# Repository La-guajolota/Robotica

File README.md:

# 🤖 Robotics Design Toolkit 
*Resources for comprehensive robot design: Kinematics, Dynamics, Mechanisms and more*

---

A curated repository with tools, algorithms, simulations and educational resources for the design and analysis of robotic systems.

---

## 📂 Folder Structure

This repository is organized into the following main directories:

- **`computes/`**: Contains scripts and algorithms for kinematic and dynamic calculations.
- **`IA/`**: Artificial Intelligence algorithms and examples.
- **`proyects/`**: Various robotics projects, from CAD designs to software implementations.
- **`raspberry5/`**: Scripts and resources for the Raspberry Pi 5.
- **`vision/`**: Computer vision algorithms and examples.

---

## 🚀 Getting Started

To get started with this repository, you can clone it to your local machine:

```bash
git clone https://github.com/your-username/robotics-design-toolkit.git
```

Once cloned, you can explore the different folders and use the resources available in each of them. For more information on how to use the content of a specific folder, please refer to the `README.md` file in that folder.

---

## 🤝 Contributing

Contributions are welcome! If you have any ideas, suggestions or improvements, please open an issue or submit a pull request.

---

## 📜 License

This repository is licensed under the [MIT License](LICENSE).

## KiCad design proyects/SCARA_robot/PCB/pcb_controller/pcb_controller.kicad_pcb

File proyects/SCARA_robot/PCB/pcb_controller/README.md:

# ⚡️ PCB Controller

This directory contains the KiCad project for the robot's controller PCB.

---

## 📂 Files

- **`pcb_controller.kicad_pro`**: The main KiCad project file.
- **`pcb_controller.kicad_sch`**: The schematic for the PCB.
- **`pcb_controller.kicad_pcb`**: The PCB layout.
- **`bom/`**: Contains the Bill of Materials for the PCB.
- **`production/`**: Contains the Gerber files for manufacturing the PCB.
- **`modules.pretty/`**: Contains custom footprints used in the project.
- **`pcb_controller-backups/`**: Contains backups of the project.

---

## 🚀 Usage

You can open the `pcb_controller.kicad_pro` file in KiCad to view and edit the schematic and PCB layout. The Gerber files in the `production` directory can be used to manufacture the PCB.

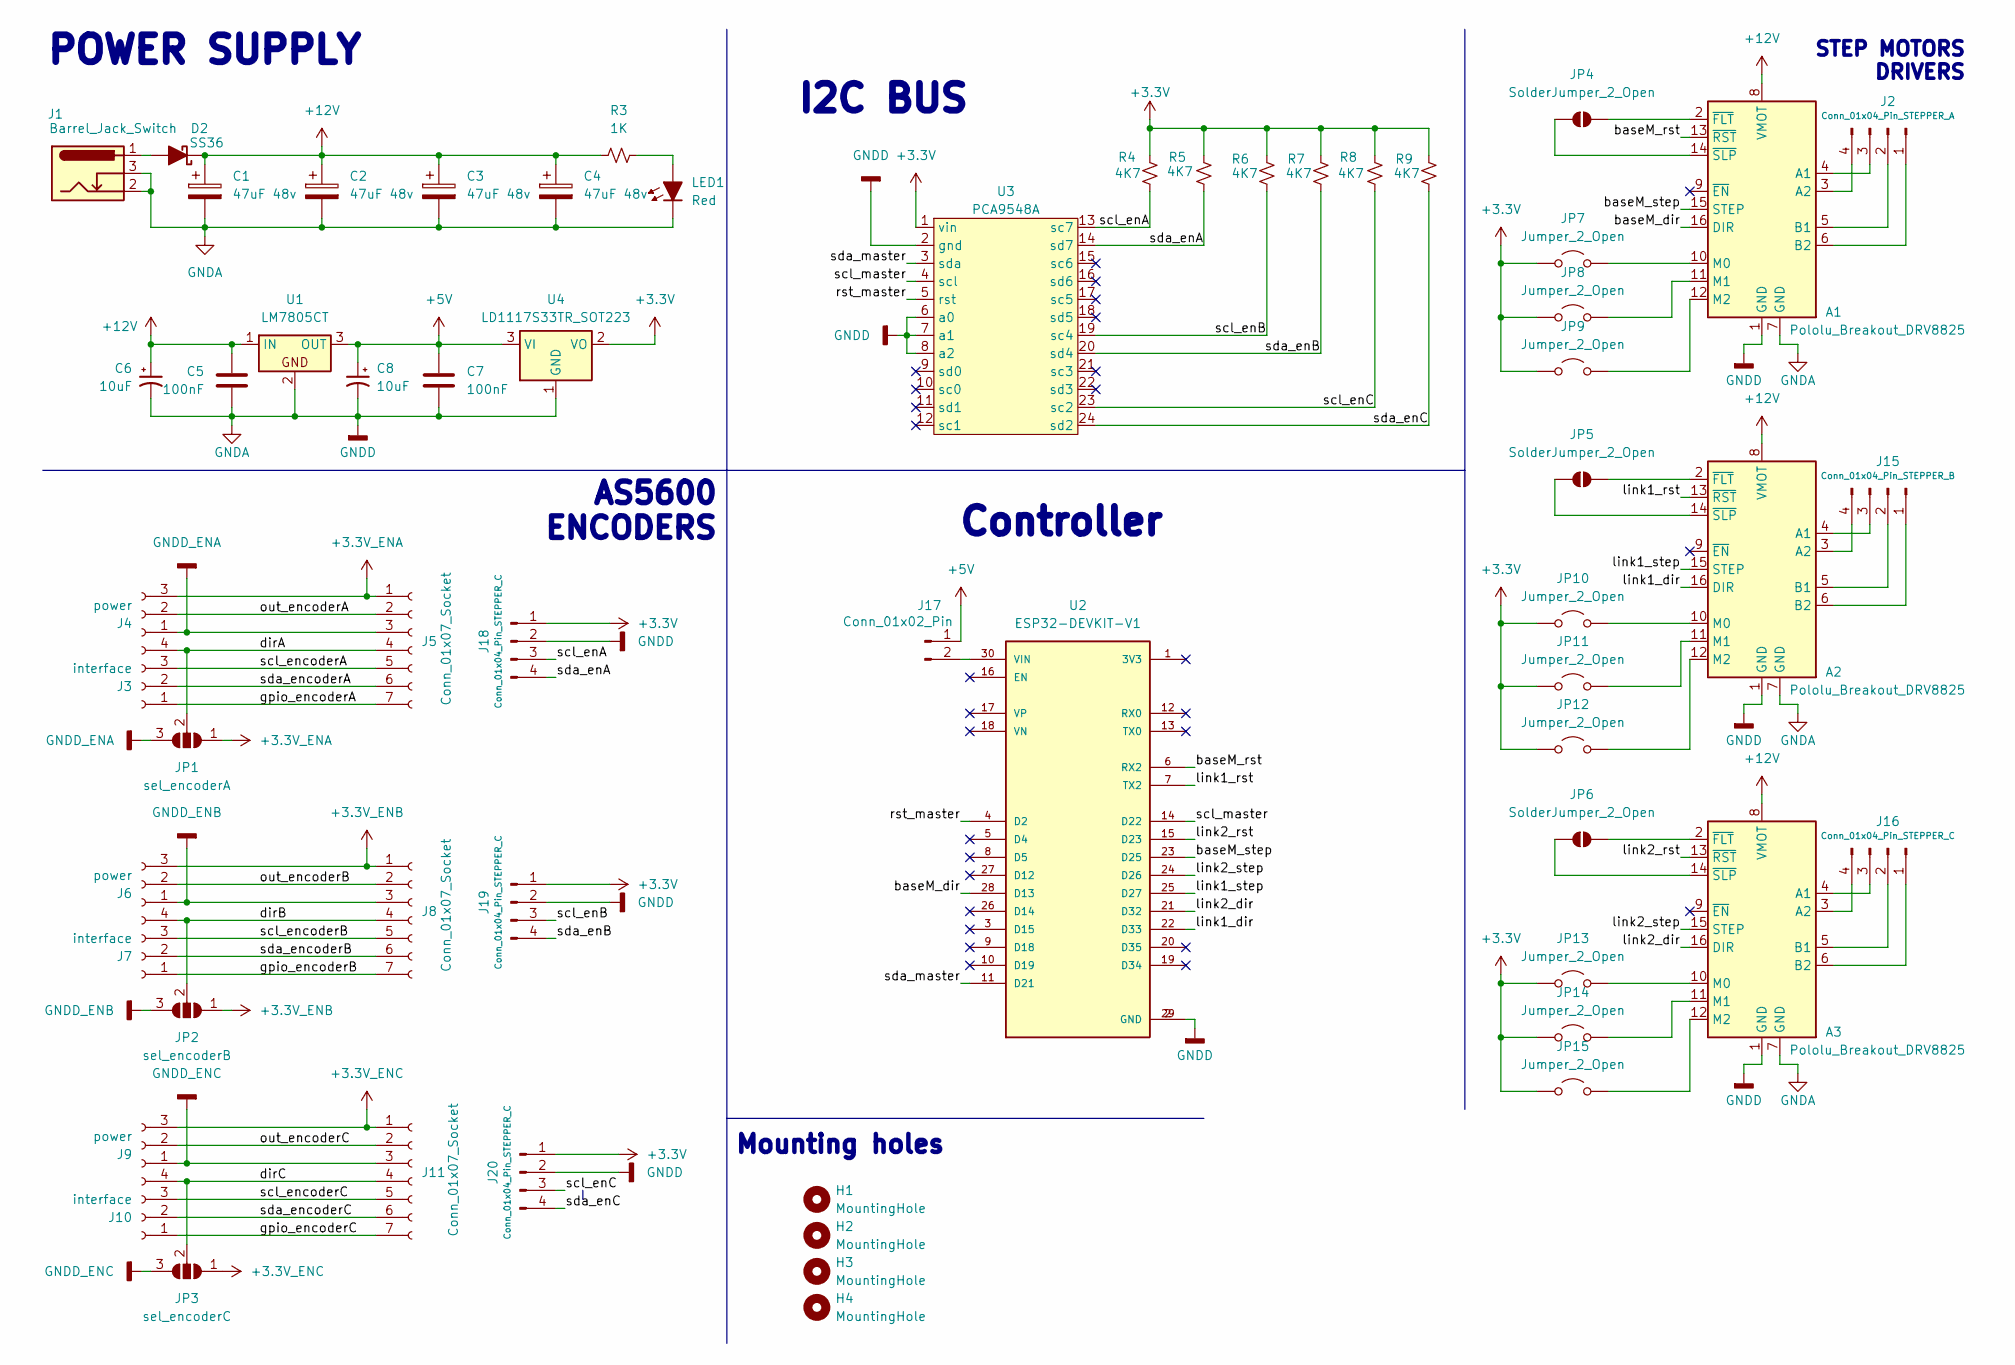
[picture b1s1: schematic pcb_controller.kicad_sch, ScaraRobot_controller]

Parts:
A1, A2, A3: Pololu_Breakout_DRV8825; Pololu_Breakout-16_15.2x20.3mm
C1, C2, C3, C4: 47uF 48v; CP_Radial_D10.0mm_P5.00mm
C5, C7: 100nF; C_Disc_D4.7mm_W2.5mm_P5.00mm
C6, C8: 10uF; CP_Radial_D5.0mm_P2.00mm
D2: SS36; D_2114_3652Metric_Pad1.85x3.75mm_HandSolder
H1, H2, H3, H4: MountingHole; MountingHole_3.2mm_M3_ISO14580
J1: Barrel_Jack_Switch; BarrelJack_CUI_PJ-102AH_Horizontal
J2: Conn_01x04_Pin_STEPPER_A; JST_XH_B4B-XH-AM_1x04_P2.50mm_Vertical
J3, J7, J10: interface; PinHeader_1x04_P2.54mm_Vertical
J4, J6, J9: power; PinHeader_1x03_P2.54mm_Vertical
J5, J8, J11: Conn_01x07_Socket; JST_XH_S7B-XH-A-1_1x07_P2.50mm_Horizontal
J15: Conn_01x04_Pin_STEPPER_B; JST_XH_B4B-XH-AM_1x04_P2.50mm_Vertical
J16, J18, J19, J20: Conn_01x04_Pin_STEPPER_C; JST_XH_B4B-XH-AM_1x04_P2.50mm_Vertical
J17: Conn_01x02_Pin; PinSocket_1x02_P2.54mm_Vertical
JP1: sel_encoderA; SolderJumper-3_P1.3mm_Open_RoundedPad1.0x1.5mm
JP2: sel_encoderB; SolderJumper-3_P1.3mm_Open_RoundedPad1.0x1.5mm
JP3: sel_encoderC; SolderJumper-3_P1.3mm_Open_RoundedPad1.0x1.5mm
JP4, JP5, JP6: SolderJumper_2_Open; SolderJumper-2_P1.3mm_Open_RoundedPad1.0x1.5mm
JP7, JP8, JP9, JP10, JP11, JP12, JP13, JP14, JP15: Jumper_2_Open; Jumper_P2.54mm_D0.7mm
LED1: Red; LED_D5.0mm
R3: 1K; R_Axial_DIN0207_L6.3mm_D2.5mm_P7.62mm_Horizontal
R4, R5, R6, R7, R8, R9: 4K7; R_Axial_DIN0207_L6.3mm_D2.5mm_P10.16mm_Horizontal
U1: LM7805CT; TO-220-3_Horizontal
U2: ESP32-DEVKIT-V1; MODULE_ESP32_DEVKIT_V1; PARTREV N/A
U3: PCA9548A; TCA9548A
U4: LD1117S33TR_SOT223; SOT-223-3_TabPin2

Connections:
+3.3V: J18.1, J19.1, J20.1, JP7.1 (A), JP8.1 (A), JP9.1 (A), JP10.1 (A), JP11.1 (A), JP12.1 (A), JP13.1 (A), JP14.1 (A), JP15.1 (A), R4.1, R5.1, R6.1, R7.1, R8.1, R9.1, U3.1 (vin), U4.2 (VO)
+3.3V_ENA: J4.3, J5.1, JP1.1 (A)
+3.3V_ENB: J6.3, J8.1, JP2.1 (A)
+3.3V_ENC: J9.3, J11.1, JP3.1 (A)
+5V: C7.2, C8.1, J17.1, U1.3 (OUT), U4.3 (VI)
+12V: A1.8 (VMOT), A2.8 (VMOT), A3.8 (VMOT), C1.1, C2.1, C3.1, C4.1, C5.2, C6.1, D2.1 (K), R3.1, U1.1 (IN)
/baseM_dir: A1.16 (DIR), U2.28 (D13)
/baseM_rst: A1.13 (~RST), U2.6 (RX2)
/baseM_step: A1.15 (STEP), U2.23 (D25)
/dirA: J3.4, J5.4, JP1.2 (C)
/dirB: J7.4, J8.4, JP2.2 (C)
/dirC: J10.4, J11.4, JP3.2 (C)
/gpio_encoderA: J3.1, J5.7
/gpio_encoderB: J7.1, J8.7
/gpio_encoderC: J10.1, J11.7
/link1_dir: A2.16 (DIR), U2.22 (D33)
/link1_rst: A2.13 (~RST), U2.7 (TX2)
/link1_step: A2.15 (STEP), U2.25 (D27)
/link2_dir: A3.16 (DIR), U2.21 (D32)
/link2_rst: A3.13 (~RST), U2.15 (D23)
/link2_step: A3.15 (STEP), U2.24 (D26)
/out_encoderA: J4.2, J5.2
/out_encoderB: J6.2, J8.2
/out_encoderC: J9.2, J11.2
/rst_master: U2.4 (D2), U3.5 (rst)
/scl_enA: J18.3, R4.2, U3.13 (sc7)
/scl_enB: J19.3, R6.2, U3.19 (sc4)
/scl_enC: J20.3, R8.2, U3.23 (sc2)
/scl_encoderA: J3.3, J5.5
/scl_encoderB: J7.3, J8.5
/scl_encoderC: J10.3, J11.5
/scl_master: U2.14 (D22), U3.4 (scl)
/sda_enA: J18.4, R5.2, U3.14 (sd7)
/sda_enB: J19.4, R7.2, U3.20 (sd4)
/sda_enC: J20.4, R9.2, U3.24 (sd2)
/sda_encoderA: J3.2, J5.6
/sda_encoderB: J7.2, J8.6
/sda_encoderC: J10.2, J11.6
/sda_master: U2.11 (D21), U3.3 (sda)
GNDA: A1.1 (GND), A1.7 (GND), A2.1 (GND), A2.7 (GND), A3.1 (GND), A3.7 (GND), C1.2, C2.2, C3.2, C4.2, C5.1, C6.2, C7.1, C8.2, J1.2, J1.3, J18.2, J19.2, J20.2, LED1.1 (K), U1.2, U2.2 (GND), U2.29 (GND), U3.2 (gnd), U3.6 (a0), U3.7 (a1), U3.8 (a2), U4.1 (GND)
GNDD_ENA: J4.1, J5.3, JP1.3 (B)
GNDD_ENB: J6.1, J8.3, JP2.3 (B)
GNDD_ENC: J9.1, J11.3, JP3.3 (B)
unnamed: A1.4 (A1), J2.3
unnamed: A1.3 (A2), J2.4
unnamed: A1.5 (B1), J2.2
unnamed: A1.6 (B2), J2.1
unnamed: A1.10 (M0), JP7.2 (B)
unnamed: A1.11 (M1), JP8.2 (B)
unnamed: A1.12 (M2), JP9.2 (B)
unnamed: A1.2 (~FLT), JP4.1 (A)
unnamed: A1.14 (~SLP), JP4.2 (B)
unnamed: A2.4 (A1), J15.3
unnamed: A2.3 (A2), J15.4
unnamed: A2.5 (B1), J15.2
unnamed: A2.6 (B2), J15.1
unnamed: A2.10 (M0), JP10.2 (B)
unnamed: A2.11 (M1), JP11.2 (B)
unnamed: A2.12 (M2), JP12.2 (B)
unnamed: A2.2 (~FLT), JP5.1 (A)
unnamed: A2.14 (~SLP), JP5.2 (B)
unnamed: A3.4 (A1), J16.3
unnamed: A3.3 (A2), J16.4
unnamed: A3.5 (B1), J16.2
unnamed: A3.6 (B2), J16.1
unnamed: A3.10 (M0), JP13.2 (B)
unnamed: A3.11 (M1), JP14.2 (B)
unnamed: A3.12 (M2), JP15.2 (B)
unnamed: A3.2 (~FLT), JP6.1 (A)
unnamed: A3.14 (~SLP), JP6.2 (B)
unnamed: D2.2 (A), J1.1
unnamed: J17.2, U2.30 (VIN)
unnamed: LED1.2 (A), R3.2

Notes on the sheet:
STEP MOTORS DRIVERS
Controller
POWER SUPPLY
I2C BUS
Mounting holes
AS5600 ENCODERS

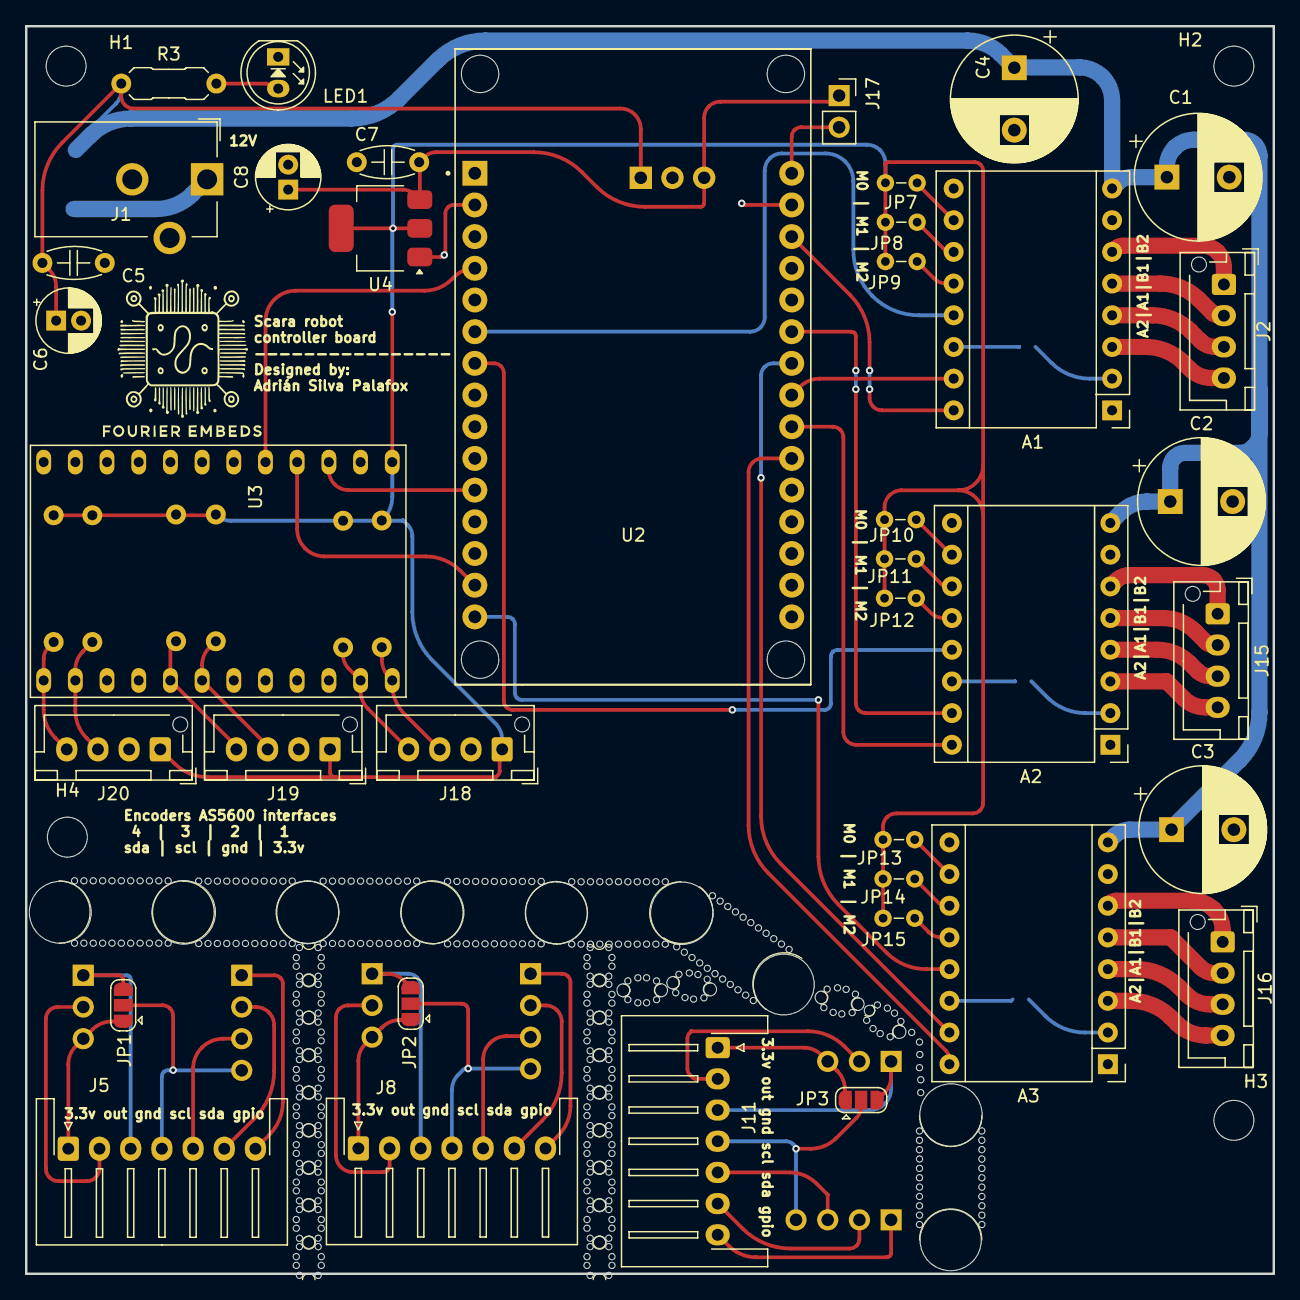
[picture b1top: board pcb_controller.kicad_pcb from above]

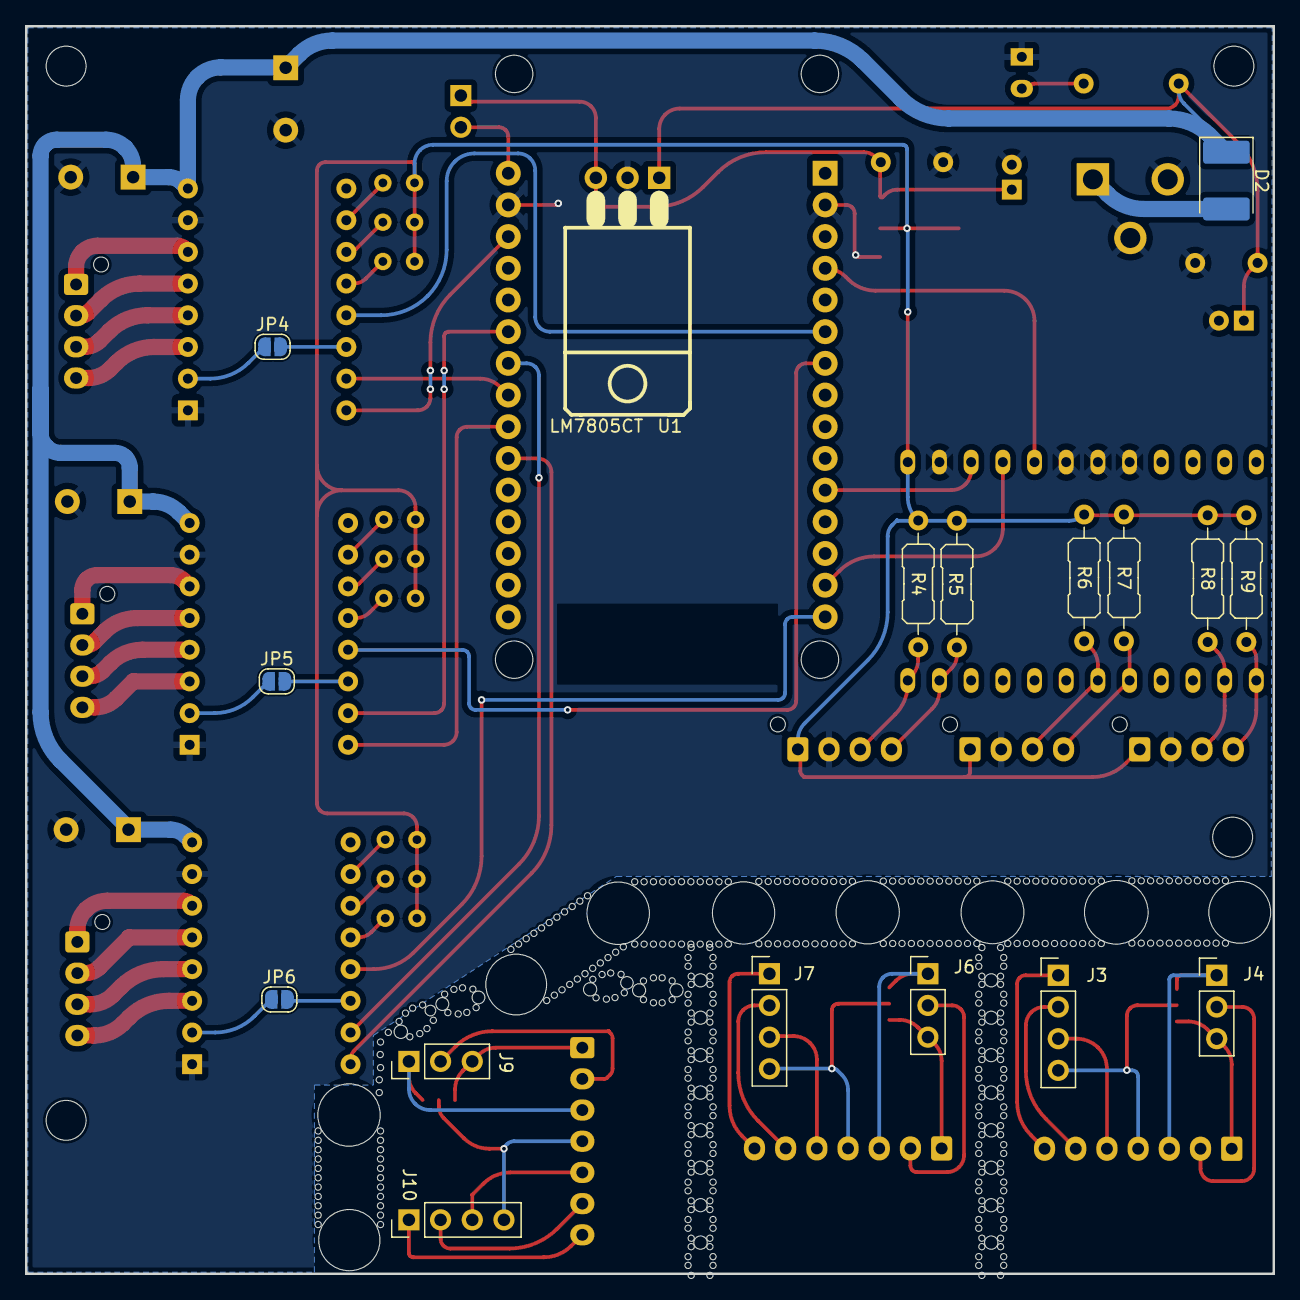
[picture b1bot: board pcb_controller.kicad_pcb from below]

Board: 2 copper layers, 100.0 x 100.0 mm, 90 parts (17 on the bottom side), 73 nets.

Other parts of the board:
Adrián Silva Palafox: LOGO; LOGOFOURIEREMBEDS
mouse-bite-1mm-slot, mouse-bite-1mm-slot#2, mouse-bite-1mm-slot#3, mouse-bite-1mm-slot#4, mouse-bite-1mm-slot#5, mouse-bite-1mm-slot#6, mouse-bite-1mm-slot#7, mouse-bite-1mm-slot#8, mouse-bite-1mm-slot#9, mouse-bite-1mm-slot#10, mouse-bite-1mm-slot#11, mouse-bite-1mm-slot#12, mouse-bite-1mm-slot#13, mouse-bite-1mm-slot#14, mouse-bite-1mm-slot#15, mouse-bite-1mm-slot#16, mouse-bite-1mm-slot#17, mouse-bite-1mm-slot#18, mouse-bite-1mm-slot#19, mouse-bite-1mm-slot#20, mouse-bite-1mm-slot#21, mouse-bite-1mm-slot#22: VAL**; mouse-bite-1mm
mouse-bite-5mm-slot, mouse-bite-5mm-slot#2, mouse-bite-5mm-slot#3, mouse-bite-5mm-slot#4, mouse-bite-5mm-slot#5, mouse-bite-5mm-slot#6, mouse-bite-5mm-slot#7: VAL**; mouse-bite-5mm-slot

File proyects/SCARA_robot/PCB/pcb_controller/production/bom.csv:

Designator,Footprint,Quantity,Value,LCSC Part #
"_6, _5, _4, _3, _2, ",,6,,
"A1, A2, A3",Pololu_Breakout-16_15.2x20.3mm,3,Pololu_Breakout_DRV8825,
"C1, C2, C3, C4",CP_Radial_D10.0mm_P5.00mm,4,47uF 48v,
"C5, C7",C_Disc_D4.7mm_W2.5mm_P5.00mm,2,100nF,
"C6, C8",CP_Radial_D5.0mm_P2.00mm,2,10uF,
D2,2114,1,SS36,
J1,BarrelJack_CUI_PJ-102AH_Horizontal,1,Barrel_Jack_Switch,
"J10, J3, J7",PinHeader_1x04_P2.54mm_Vertical,3,interface,
"J11, J5, J8",JST_XH_S7B-XH-A-1_1x07_P2.50mm_Horizontal,3,Conn_01x07_Socket,
J15,JST_XH_B4B-XH-AM_1x04_P2.50mm_Vertical,1,Conn_01x04_Pin_STEPPER_B,
"J16, J18, J19, J20",JST_XH_B4B-XH-AM_1x04_P2.50mm_Vertical,4,Conn_01x04_Pin_STEPPER_C,
J17,PinSocket_1x02_P2.54mm_Vertical,1,Conn_01x02_Pin,
J2,JST_XH_B4B-XH-AM_1x04_P2.50mm_Vertical,1,Conn_01x04_Pin_STEPPER_A,
"J4, J6, J9",PinHeader_1x03_P2.54mm_Vertical,3,power,
"JP10, JP11, JP12, JP13, JP14, JP15, JP7, JP8, JP9",Jumper_P2.54mm_D0.7mm,9,Jumper_2_Open,
LED1,LED_D5.0mm,1,Red,
"MOUSE-BITE-1MM-SLOT_22, MOUSE-BITE-1MM-SLOT_21, MOUSE-BITE-1MM-SLOT_20, MOUSE-BITE-1MM-SLOT_19, MOUSE-BITE-1MM-SLOT_18, MOUSE-BITE-1MM-SLOT_17, MOUSE-BITE-1MM-SLOT_16, MOUSE-BITE-1MM-SLOT_15, MOUSE-BITE-1MM-SLOT_14, MOUSE-BITE-1MM-SLOT_13, MOUSE-BITE-1MM-SLOT_12, MOUSE-BITE-1MM-SLOT_11, MOUSE-BITE-1MM-SLOT_10, MOUSE-BITE-1MM-SLOT_9, MOUSE-BITE-1MM-SLOT_8, MOUSE-BITE-1MM-SLOT_7, MOUSE-BITE-1MM-SLOT_6, MOUSE-BITE-1MM-SLOT_5, MOUSE-BITE-1MM-SLOT_4, MOUSE-BITE-1MM-SLOT_3, MOUSE-BITE-1MM-SLOT_2, MOUSE-BITE-1MM-SLOT",mouse-bite-1mm,22,VAL**,
"MOUSE-BITE-5MM-SLOT_7, MOUSE-BITE-5MM-SLOT_6, MOUSE-BITE-5MM-SLOT_5, MOUSE-BITE-5MM-SLOT_4, MOUSE-BITE-5MM-SLOT_3, MOUSE-BITE-5MM-SLOT_2, MOUSE-BITE-5MM-SLOT",mouse-bite-5mm-slot,7,VAL**,
R3,R_Axial_DIN0207_L6.3mm_D2.5mm_P7.62mm_Horizontal,1,1K,
"R4, R5, R6, R7, R8, R9",R_Axial_DIN0207_L6.3mm_D2.5mm_P10.16mm_Horizontal,6,4K7,
U1,TO-220-3_Horizontal,1,LM7805CT,
U2,MODULE_ESP32_DEVKIT_V1,1,ESP32-DEVKIT-V1,
U3,TCA9548A,1,PCA9548A,
U4,SOT-223-3_TabPin2,1,LD1117S33TR_SOT223,

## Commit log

2025-03-09 pri tandar
2025-03-09 seg tandar
2025-03-09 correcion en gitignore
2025-03-09 Dejar de trackear carpetas añadidas a .gitignore
2025-03-09 Dejar de trackear carpetas añadidas a .gitignore2
2025-03-11 new file: "cinem\303\241tica/matriz_homogenea.py" new file: espacio de trabajo.jpg
2025-03-11 new file: "cinem\303\241tica/eslabon_obj.py"
2025-03-14 new file: Examen Periodo 1-2025-fusionado.pdf modified: Root_finding/Newton_Raphson_multiVar.py
2025-03-14 new file: "cinem\303\241tica/dh.py" new file: examen1/problema2_0.jpeg new file: examen1/problema2_1.jpeg new file: examen1/problema2_2.jpeg new file: examen1/problema2_3.png
2025-03-14 modified: "cinem\303\241tica/dh.py"
2025-03-15 actualizacion del gitignore
2025-03-15 deleted: Examen Periodo 1-2025-fusionado.pdf modified: "cinem\303\241tica/dh.py"
2025-03-15 deleted: examen1/problema2_0.jpeg deleted: examen1/problema2_1.jpeg deleted: examen1/problema2_2.jpeg deleted: examen1/problema2_3.png
2025-04-02 modified: Root_finding/genpy/lib/python3.12/site-packages/numpy/fft/__pycache__/__init__.cpython-312.pyc modified: Root_finding/genpy/lib/python3.12/site-packages/numpy/fft/__pycache__/_helper.cpytho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
2025-04-02 modified: vision/botones_segment.py new file: vision/btns2.png modified: vision/convoluciones.py new file: vision/convoluciones.txt
2025-04-04 new file: IA/ex_ann_1.py
2025-04-04 new file: IA/cats-vs-dogs-classification.ipynb new file: IA/catvsdog.py
2025-04-04 deleted: IA/catvsdog.py
2025-04-06 modified: .gitignore deleted: genpy env deleted
2025-04-09 modified: IA/cats-vs-dogs-classification.ipynb new file: vision/practicas/hibrido.ipynb new file: vision/practicas/manos.py
2025-04-19 ROS SCARA MICROROS
2025-04-21 custom service clietn nodo
2025-04-25 Liscencia agregada
2025-04-28 cración de carpeta y bases para el proyecto de segundo parcial
2025-04-28 optención de base de datos de imagenes desde kaggle
2025-04-28 Entrnamiento del modelo, prueba con magenes random, evaluación con camara web
2025-04-28 Renombramiento de READ.dm a README.md
2025-04-28 Reorganización de archivos en carpetas
2025-04-28 modelo exportado a tensorflow lite
2025-04-29 Modified README.md Modified src scripts' name
2025-05-04 Readme updated
2025-05-06 pixels to in
2025-05-09 primer comit
2025-05-09 Actualizacion
2025-05-09 web-cam-rasp5
2025-05-09 requirements - raspberrypi5
2025-05-09 rasp5_requirements
2025-05-11 pcb_kicad
2025-05-11 schematic ready
2025-05-11 schematic and footprints ready
2025-05-11 pcb designed phase 1
2025-05-12 pcb designed phase 2
2025-05-12 pcb designed phase 3
2025-05-12 pcb finalizada
2025-05-12 pcb finalizada, todo revisar
2025-05-12 pcb finalizada y ordenada
2025-05-12 modificación de pines de acuerdo a la pcb
2025-05-13 update pcb
2025-05-13 fotos a zip
2025-05-13 update codigo
2025-05-13 update branch
2025-05-13 update tca9548a library
2025-05-13 rediseño de PCB
2025-05-16 Drawer robot first commit
2025-05-18 Encoders' shield added
2025-05-18 my_robot with urdf example}
2025-05-18 my_robot with urdf examples
2025-05-19 my_car_description pkg
2025-05-19 my_car_description pkg reordenación de carpetas
2025-05-19 reorganization of folders
2025-05-20 rename
2025-05-26 WIFI transfer and TCA9548A integration
2025-05-26 casi me doxeo
2025-05-26 correccion
2025-05-26 vision_demo_ROS
2025-06-13 version1 scararobot
2025-06-16 backup
2025-06-16 Ignore firebase cedentials
2025-06-16 código de la rasp en proyecto SCARA
2025-06-16 raspberry software SCARA
2025-06-16 autor dani
2025-06-17 statemachine Scara coordination
2025-06-17 statemachine Scara coordination debug1
2025-06-18 statemachine Scara coordination debug2
2025-06-19 statemachine Scara coordination debug3
2025-06-27 proyecto final
2025-06-27 ros2 workspace
2025-10-23 documentation updated
